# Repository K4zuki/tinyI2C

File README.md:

tinyI2C{-}
=======

This is a tiny UART-I2C converter software/hardware project using mbed conpatible microcontrollers.
The module converts UART command packets into I2C/SPI protocol or GPIO to read/write with
configurable pull-up/pull-down modes.

- the "FTDI" USB-UART cable to connect to host PC; from PC the module look only an USB-Serial port
    - up to 115200 boudrate UART to communicate
- up to 4 channel I2C ports with selectable speed
- one SPI port with 8/16 bits word, also selectable speed
- up to 2 x 8bit, General Purpose IO ports

```
TinyI2C/         <-- root
├── doc/      <-- document source
├── gui/      <-- PyQt4 based GUI source codes
├── mbed/     <-- mbed source codes
├── pcb/      <-- PCB design files for eagle
└── python/   <-- python module code with standalone test program
```

# Requirement
- Python 3
  `apt-get install python3`
- PySerial
  `pip3 install pyserial`
* mbed microcontrollers using LPC824(recommended)/LPC1768/LPC11U24/LPC11U35
  see [mbed.org](developer.mbed.org)

# Install
1. install python 3.3+ on your PC
2. install PySerial
3. (Windows only) if you use LpcXpresso 824 then install [mbed Serial port driver](http://developer.mbed.org/handbook/Windows-serial-configuration)

# Usage
1. write mbed program into your mbed
2. connect mbed to PC via Serial port
3. start gui software
4. select Serial port from dropdown list
5. you will be able to use up to 4 channels of I2C slaves and more!
    * check PinOut for your usage! 

# Demo
  try `python/test.py`

## Demo GUI
GUI source codes placed in `gui/` which requires compilation
 (for now, _do it yourself_ basis).

GUI setup requires:

- PyQt5
- pyinstaller

```
$ pip3 install pyqt5 pyinstaller
```

### Compile GUI
On project root,
```
$ make gui
```

### Run GUI
On project root,
```
$ dist/TinyI2C
```

# Command set and protocol
- _this command character as well as packet structure is inspired(some copied) from
NXP Semiconductor's UART-I2C converter/controller, named **SC18IM700**._

- the command packet starts/ends with few number of characters: for starting(`head`)
character there are several choices but ending(`tail`) is always `'P'`, 0x50 in hex.
    - if only sending 'P', `tinyI2C` makes stop condition pulse (**without start condition**)
  on currently selected I2C bus and returns "ok" return packet.
- the `tinyI2C` watches its UART port \_Forever until_ it receives `tail`
  and counts received packet length by bytes (`plength`).
  then searches first character of the packet whether if matches one of registered `head` character.
    - if it does not match with any of valid `head` the device returns
  "command is not implemented" return packet.
- if valid head found it checks `plength-2` which is actual data packet length.
    - if you send an invalid packet, the device returns "bad packet" return packet.

## I2C
### `'S'` 0x53 I2C-bus START
### `'P'` 0x50 I2C-bus STOP, end of packet
- the protocol starts from `'S'`, which makes start condition on I2C bus, followed by 7bit I2C slave address and read(1)/write(0) command bit and,
  - to *Write* data into slave device: send data length to write(1~255) and actual data
  - to *Read* data from slave device: send data length to read(1~255)
- ends with sending `'P'` which makes stop condition on the bus
- return packet depends on command:
  - first, `"ACK"` or `"NAK"` depends on response from slave
  - *Read*: read data in hex sting (0xAA -> "AA") separated by ',' and ends by `ok`
  - *Write*: `ok`

- command packet: write 4 bytes to slave at 0x80(8bit)

| head  | slave address(W) | data length |          binary data to write           | tail  |
|:-----:|:----------------:|:-----------:|:---------------------------------------:|:-----:|
|   S   |    0x\_8 \_0     |  0x\_0 \_4  |    0x_D \_E \_A \_D \_B \_E \_A \_F     |   P   |
| `'S'` |      `'80'`      |   `'04'`    |              `'=>:=;>:?'`               | `'P'` |
| 0x53  |    0x38 0x30     |  0x30 0x34  | 0x3D 0x3E 0x3A 0x3D 0x3B 0x3E 0x3A 0x3F | 0x50  |

- return packet

| result | head  | delimiter | tail |
|:------:|:-----:|:---------:|:----:|
| sucess | "ACK" |     ,     | "ok" |
|  fail  | "NAK" |     ,     | "ok" |

- command packet: read 4 bytes from slave at 0x80(8bit)

| head | slave address(R\) | data length | tail |
|:----:|:-----------------:|:-----------:|:----:|
|  S   |     0x\_8 \_1     |  0x\_0 \_4  |  P   |

- return packet

| result | head  | delimiter |               data                | tail |
|:------:|:-----:|:---------:|:---------------------------------:|:----:|
| sucess | "ACK" |     ,     | actual data: "AA","BB","CC","DD", | "ok" |
|  fail  | "NAK" |     ,     | dummy data: "C4","FE","E0","CA",  | "ok" |

- command packet: write and read 4 bytes to/from slave at 0x80(8bit)

| head | slave address(W) | data length |       binary data to write       | repeated start | slave address(R\) | data length | tail |
|:----:|:----------------:|:-----------:|:--------------------------------:|:--------------:|:-----------------:|:-----------:|:----:|
|  S   |    0x\_8 \_0     |  0x\_0 \_4  | 0x_D \_E \_A \_D \_B \_E \_A \_F |       S        |     0x\_8 \_1     |  0x\_0 \_4  |  P   |

- return packet

| result | head  | delimiter |               data                | tail |
|:------:|:-----:|:---------:|:---------------------------------:|:----:|
| sucess | "ACK" |     ,     | actual data: "AA","BB","CC","DD", | "ok" |
|  fail  | "NAK" |     ,     | dummy data: "C4","FE","E0","CA",  | "ok" |

### `'C'` 0x43 change channel
- you can select I2C channel by sending `'C'` and channel number `'0'`to`'3'` with `tail` char.

| head | channel | tail |
|:----:|:-------:|:----:|
|  C   |   '0'   |  P   |
|  C   |   '1'   |  P   |
|  C   |   '2'   |  P   |
|  C   |   '3'   |  P   |

## SPI
### `'E'` 0x45 SPI transfer start

- minimum plength=8

| head | data length(W) | data length(R\) | binary data to write | tail |
|:----:|:--------------:|:---------------:|:--------------------:|:----:|
|  E   |   0x\_0 \_1    |    0x\_0 \_0    |      0x\_D \_E       |  P   |

- minimum plength=10(16bit)

| head | data length(W) | data length(R\) | binary data to write | tail |
|:----:|:--------------:|:---------------:|:--------------------:|:----:|
|  E   |   0x\_0 \_1    |    0x\_0 \_0    |   0x_D \_E \_A \_D   |  P   |

- write and read

| head | data length(W) | data length(R\) |       binary data to write       | tail |
|:----:|:--------------:|:---------------:|:--------------------------------:|:----:|
|  E   |   0x\_0 \_4    |    0x\_0 \_4    | 0x_D \_E \_A \_D \_B \_E \_A \_F |  P   |

<!--
~~~
/*
"0|   1   2|   3   4|   5   6  7  8  9 10 11 12|13" //plength=14
"E| 0x\_0 \_1| 0x\_0 \_0| 0x_D \_E| P"                   //minimum plength=8
"E| 0x\_0 \_1| 0x\_0 \_0| 0x_D \_E|_A \_D| P"             //minimum plength=10(16bit)
"E| 0x\_0 \_4| 0x\_0 \_0| 0x_D \_E \_A \_D \_B \_E \_A \_F| P" //write
"E| 0x\_0 \_4| 0x\_0 \_4| 0x_D \_E \_A \_D \_B \_E \_A \_F| P" //write and read
*/
~~~
-->

## GPIO
This is a subset of [R/W commands](#internal-registers); only access GPIO's status registers.

### `'I'` 0x49 read GPIO port register
### `'O'` 0x4F write to GPIO port register

| head | GPIO | tail |
|:----:|:----:|:----:|
|  I   | '0'  |  P   |
|  I   | '1'  |  P   |

| head | GPIO |   data    | tail |
|:----:|:----:|:---------:|:----:|
|  O   | '0'  | 0x\_A \_A |  P   |
|  O   | '1'  | 0x\_A \_A |  P   |

| register | name in python | purpose          |
|:--------:|:--------------:|:-----------------|
|    0     |   GPIO0_STAT   | status of GPIO 0 |
|    1     |   GPIO1_STAT   | status of GPIO 1 |

## Internal registers
### `'R'` 0x52 read internal register
### `'W'` 0x57 write to internal register
- single register read

| head | register | tail |
|:----:|:--------:|:----:|
|  R   |   '0'    |  P   |
|  R   |   '1'    |  P   |

- multi registers read

| head | register(1) | register(2) | ... | register(n) | tail |
|:----:|:-----------:|:-----------:|:---:|:-----------:|:----:|
|  R   |     '0'     |     '1'     | ... |     '5'     |  P   |
|  R   |     '1'     |     '0'     | ... |     '9'     |  P   |

- return packet's order is same as command packet's order

: multi registers write

| head | register(1) | register data (1) | register(2) | register data (2) | ... | register(n) | register data (n) | tail |
|:----:|:-----------:|:-----------------:|:-----------:|:-----------------:|:---:|:-----------:|:-----------------:|:----:|
|  W   |     '0'     |     0x\_A \_A     |     '1'     |     0x\_A \_B     | ... |     '5'     |     0x\_A \_D     |  P   |
|  W   |     '1'     |     0x\_A \_A     |     '0'     |     0x\_A \_B     | ... |     '9'     |     0x\_A \_D     |  P   |

- return packet's order is same as command packet's order

| register | name in python | purpose                              |
|:--------:|:--------------:|:-------------------------------------|
|    0     |    CHIP_ID     | converter's chip ID                  |
|    1     |   GPIO0_STAT   | status of GPIO 0                     |
|    2     |   GPIO1_STAT   | status of GPIO 1                     |
|    4     |   GPIO1_CONF   | GPIO 0 IO configuration              |
|    3     |   GPIO0_CONF   | GPIO 1 IO configuration              |
|    5     |    I2C_CONF    | I2C channel 1~4 speed configuration  |
|    6     |    SPI_CONF    | SPI speed and polarity configuration |

| register 0  | command | CHIP_ID                    |
|:-----------:|:-------:|:---------------------------|
| [7\.\.\.0\] |   R/W   | returns chip ID character: |
|             |         | '0'- LPC824                |
|             |         | '1'- LPC1768               |
|             |         | '2'- LPC11U24 or LPC11U35  |

| register 1  | command | GPIO0_STAT                                                          |
|:-----------:|:-------:|:--------------------------------------------------------------------|
| [7\.\.\.0\] |    R    | behavior changes depend on corresponding bit of GPIO0_CONF register |
|             |         | 1: reads output setting                                             |
|             |         | 0: reads input of the pin                                           |
|             |    W    | behavior changes depend on corresponding bit of GPIO0_CONF register |
|             |         | 1: writes data to the pin                                           |
|             |         | 0: do nothing                                                       |

| register 2  | command | GPIO1_STAT                                                           |
|:-----------:|:-------:|:---------------------------------------------------------------------|
|             |         | **if GPIO1 is not enabled, access to this register will be ignored** |
| [7\.\.\.0\] |    R    | behavior changes depend on corresponding bit of GPIO1_CONF register  |
|             |         | 1: reads output setting                                              |
|             |         | 0: reads input of the pin                                            |
|             |    W    | behavior changes depend on corresponding bit of GPIO1_CONF register  |
|             |         | 1: writes data to the pin                                            |
|             |         | 0: do nothing                                                        |

| register 3  | command | GPIO0_CONF                                                                                    |
|:-----------:|:-------:|:----------------------------------------------------------------------------------------------|
| [7\.\.\.0\] |    R    | Reads each pin's Input/Output conditions:                                                     |
|             |         | 1 = the pin is set to output                                                                  |
|             |         | 0 = the pin is set to input with internal pullup                                              |
|             |    W    | Sets each pin's Input/Output configurations:                                                  |
|             |         | 1: sets the pin to an Output. output level is set by corresponding bit of GPIO0_STAT register |
|             |         | 0: sets the pin to an Input with internal pull-up connected                                   |

| register 4  | command | GPIO1_CONF                                                                                    |
|:-----------:|:-------:|:----------------------------------------------------------------------------------------------|
|             |         | **if GPIO1 is not enabled, access to this register will be ignored**                          |
| [7\.\.\.0\] |    R    | Reads each pin's Input/Output conditions:                                                     |
|             |         | 1: the pin is set to output                                                                   |
|             |         | 0: the pin is set to input with internal pullup                                               |
|             |    W    | Sets each pin's Input/Output configurations:                                                  |
|             |         | 1: sets the pin to an Output. output level is set by corresponding bit of GPIO1_STAT register |
|             |         | 0: sets the pin to an Input with internal pull-up connected                                   |

| register 5  | command | I2C_CONF                                                                                                    |
|:-----------:|:-------:|:------------------------------------------------------------------------------------------------------------|
| [7\.\.\.6\] |   R/W   | Read/Write clock configuration of I2C1                                                                      |
|             |         | 11: I2C1 is set to operate in 800kHz clock                                                                  |
|             |         | 10: I2C1 is set to operate in 600kHz clock                                                                  |
|             |         | 01: I2C1 is set to operate in 400kHz clock                                                                  |
|             |         | 00: I2C1 is set to operate in 200kHz clock                                                                  |
| [5\.\.\.4\] |         | Read/Write clock configuration of I2C2; **if I2C2 is not enabled, access to this bitfield will be ignored** |
|             |         | 11: I2C2 is set to operate in 400kHz clock                                                                  |
|             |         | 10: I2C2 is set to operate in 300kHz clock                                                                  |
|             |         | 01: I2C2 is set to operate in 200kHz clock                                                                  |
|             |         | 00: I2C2 is set to operate in 100kHz clock                                                                  |
| [3\.\.\.2\] |         | Read/Write clock configuration of I2C3; **if I2C3 is not enabled, access to this bitfield will be ignored** |
|             |         | 11: I2C3 is set to operate in 400kHz clock                                                                  |
|             |         | 10: I2C3 is set to operate in 300kHz clock                                                                  |
|             |         | 01: I2C3 is set to operate in 200kHz clock                                                                  |
|             |         | 00: I2C3 is set to operate in 100kHz clock                                                                  |
| [1\.\.\.0\] |         | Read/Write clock configuration of I2C4; **if I2C4 is not enabled, access to this bitfield will be ignored** |
|             |         | 11: I2C4 is set to operate in 400kHz clock                                                                  |
|             |         | 10: I2C4 is set to operate in 300kHz clock                                                                  |
|             |         | 01: I2C4 is set to operate in 200kHz clock                                                                  |
|             |         | 00: I2C4 is set to operate in 100kHz clock                                                                  |

| register 6  | command | SPI_CONF                                  |
|:-----------:|:-------:|:------------------------------------------|
|    [7\]     |   R/W   | Not used                                  |
| [6\.\.\.4\] |         | Read/Write clock configuration of SPI     |
|             |         | 111: SPI is set to operate in 8MHz clock  |
|             |         | 110: SPI is set to operate in 7MHz clock  |
|             |         | ...                                       |
|             |         | 001: SPI is set to operate in 2MHz clock  |
|             |         | 000: SPI is set to operate in 1MHz clock  |
|    [3\]     |         | Reads/Wreite polarity of CE print         |
|             |         | 1: CE is set to HIGH-active               |
|             |         | 0: CE is set to LOW-active                |
|    [2\]     |         | Read/Write word size setting of SPI       |
|             |         | 1: 16 bit word                            |
|             |         | 0: 8 bit word                             |
| [1\.\.\.0\] |         | Read/Write SPI mode                       |
|             |         | 11: SPI is set to operate in clock mode 3 |
|             |         | 10: SPI is set to operate in clock mode 2 |
|             |         | 01: SPI is set to operate in clock mode 1 |
|             |         | 00: SPI is set to operate in clock mode 0 |

# Contribution by
Kazuki Yamamoto ( <k.yamamoto.08136891@gmail.com> )

# License
- [CC-BY-SA](http://creativecommons.org/licenses/by-sa/4.0/legalcode)
- [CC-BY-SA 日本語](http://creativecommons.org/licenses/by-sa/2.1/jp/legalcode)

# Author

[K4zuki](https://github.com/K4zuki)

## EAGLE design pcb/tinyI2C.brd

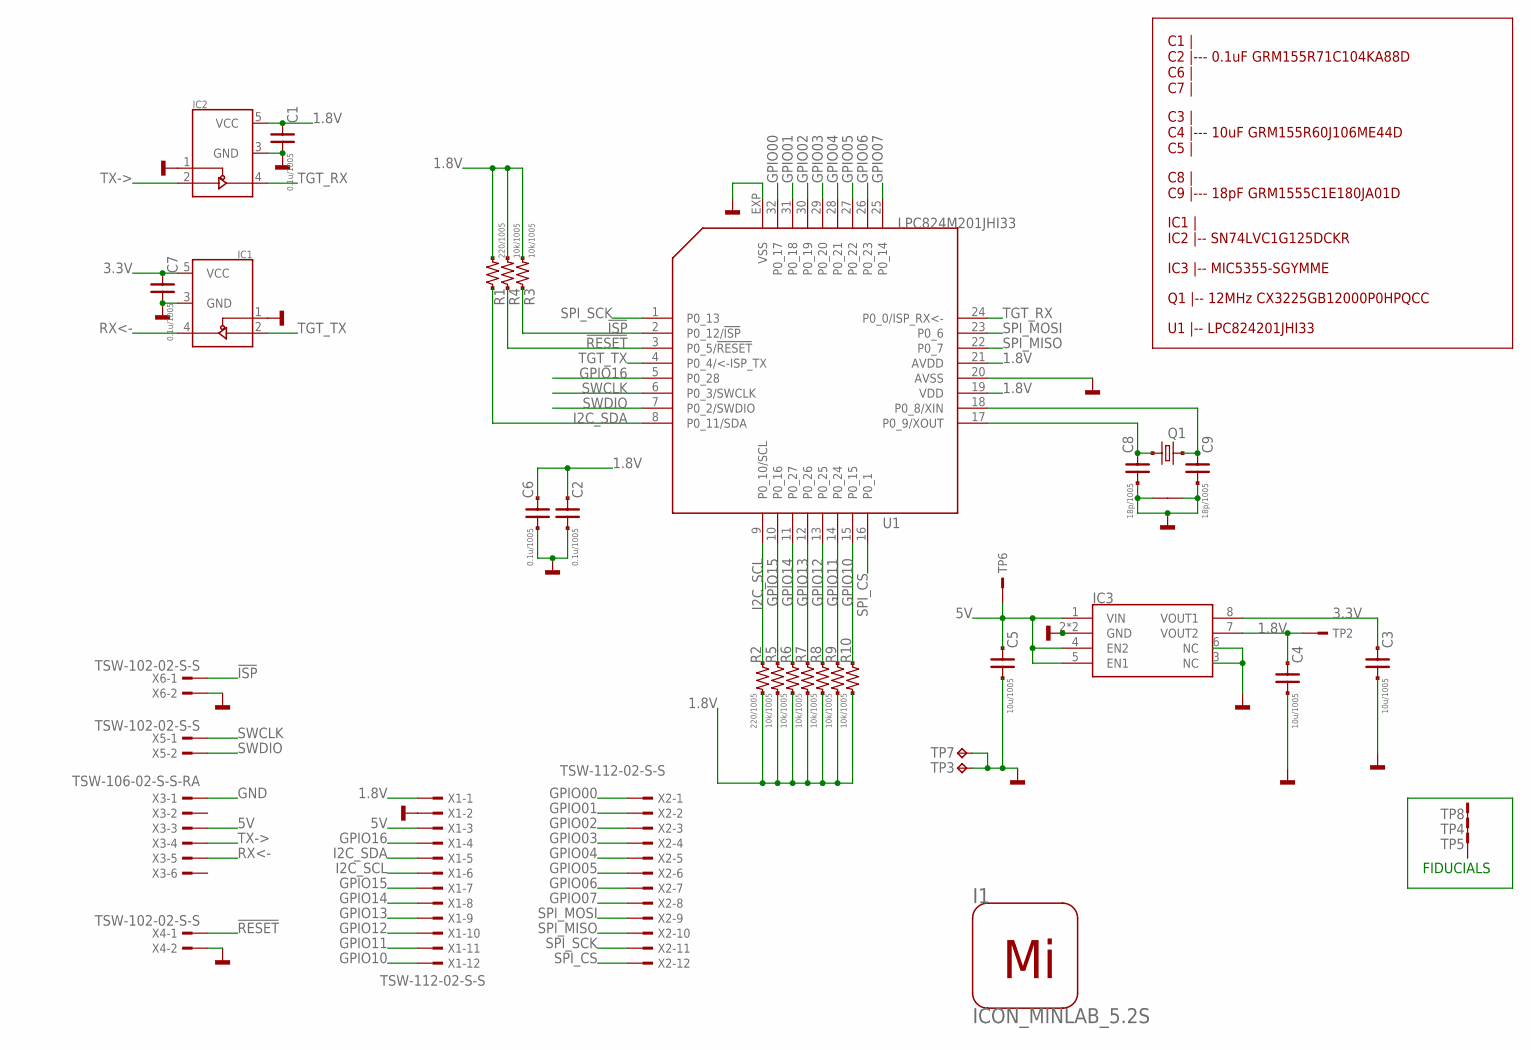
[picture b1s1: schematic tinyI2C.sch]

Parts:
C1, C2, C6, C7: 0.1u/1005; C0402
C3, C4, C5: 10u/1005; C0402
C8, C9: 18p/1005; C0402
I1: ICON_MINLAB_5.2S; ICON_MINLAB_5.2MM
IC1, IC2: 74LVC1G125_SC70; IC_05_0.635_40MIL
IC3: IC_LDO_MIC5355_3.3/1.8; IC_08_0.65_160MIL_EP
Q1: CRYSTAL4_12M_3225; CLOCK_3225
R1, R2: 220/1005; C0402
R3, R4, R5, R6, R7, R8, R9, R10: 10k/1005; C0402
TP2, TP6: TESTPAD; TP06RECT
TP3, TP7: TPTP14R; TP14R
TP4, TP5, TP8: TESTPAD_F; FIDUCIAL
U1: LPC824M201JHI33; HVQFN33
X1, X2: TSW-112-02-S-S
X3: TSW-106-02-S-S-RA
X4, X5, X6: TSW-102-02-S-S

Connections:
1.8V: C1.1, C2.1, C4.1, C6.1, IC2.5 (VCC), IC3.7 (VOUT2), R1.2, R2.2, R3.2, R4.2, R5.2, R6.2, R7.2, R8.2, R9.2, R10.2, TP2.TP, U1.19 (VDD), U1.21 (AVDD), X1.1
3.3V: C3.1, C7.1, IC1.5 (VCC), IC3.8 (VOUT1)
5V: C5.1, IC3.1 (VIN), IC3.4 (EN2), IC3.5 (EN1), TP6.TP, X1.3, X3.3
!ISP!: R3.1, U1.2 (P0_12/!ISP!), X6.1
!RESET!: R4.1, U1.3 (P0_5/!RESET!), X4.1
GND: C1.2, C2.2, C3.2, C4.2, C5.2, C6.2, C7.2, C8.2, C9.2, IC1.1 (!OE!), IC1.3 (GND), IC2.1 (!OE!), IC2.3 (GND), IC3.2 (GND), IC3.3 (NC), IC3.6 (NC), IC3.EXP (GND), Q1.2, Q1.4, TP3.TP, TP7.TP, U1.20 (AVSS), U1.EXP (VSS), X1.2, X3.1, X4.2, X6.2
GPIO00: U1.32 (P0_17), X2.1
GPIO01: U1.31 (P0_18), X2.2
GPIO02: U1.30 (P0_19), X2.3
GPIO03: U1.29 (P0_20), X2.4
GPIO04: U1.28 (P0_21), X2.5
GPIO05: U1.27 (P0_22), X2.6
GPIO06: U1.26 (P0_23), X2.7
GPIO07: U1.25 (P0_14), X2.8
GPIO10: R10.1, U1.15 (P0_15), X1.12
GPIO11: R9.1, U1.14 (P0_24), X1.11
GPIO12: R8.1, U1.13 (P0_25), X1.10
GPIO13: R7.1, U1.12 (P0_26), X1.9
GPIO14: R6.1, U1.11 (P0_27), X1.8
GPIO15: R5.1, U1.10 (P0_16), X1.7
GPIO16: U1.5 (P0_28), X1.4
I2C_SCL: R2.1, U1.9 (P0_10/SCL), X1.6
I2C_SDA: R1.1, U1.8 (P0_11/SDA), X1.5
unnamed: C8.1, Q1.1, U1.17 (P0_9/XOUT)
unnamed: C9.1, Q1.3 (2), U1.18 (P0_8/XIN)
RX<-: IC1.4 (Y), X3.5
SPI_CS: U1.16 (P0_1), X2.12
SPI_MISO: U1.22 (P0_7), X2.10
SPI_MOSI: U1.23 (P0_6), X2.9
SPI_SCK: U1.1 (P0_13), X2.11
SWCLK: U1.6 (P0_3/SWCLK), X5.1
SWDIO: U1.7 (P0_2/SWDIO), X5.2
TGT_RX: IC2.4 (Y), U1.24 (P0_0/ISP_RX<-)
TGT_TX: IC1.2 (A), U1.4 (P0_4/<-ISP_TX)
TX->: IC2.2 (A), X3.4

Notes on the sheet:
FIDUCIALS
C1 | C2 |--- 0.1uF GRM155R71C104KA88D C6 | C7 |
C3 | C4 |--- 10uF GRM155R60J106ME44D C5 |
IC1 | IC2 |-- SN74LVC1G125DCKR
IC3 |-- MIC5355-SGYMME
U1 |-- LPC824201JHI33
C8 | C9 |--- 18pF GRM1555C1E180JA01D
Q1 |-- 12MHz CX3225GB12000P0HPQCC

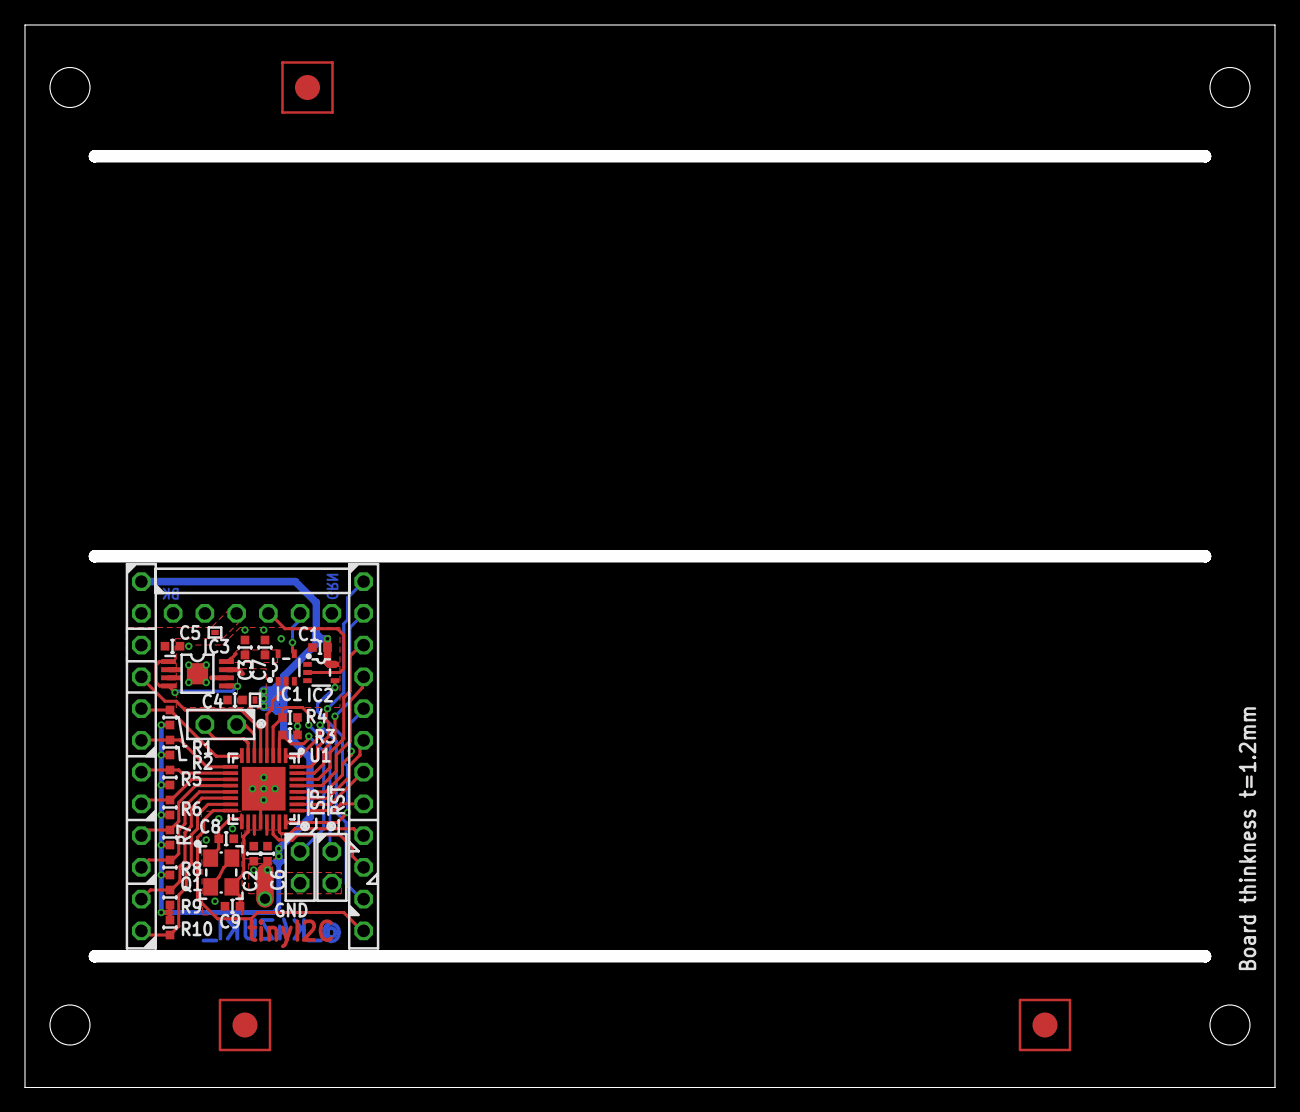
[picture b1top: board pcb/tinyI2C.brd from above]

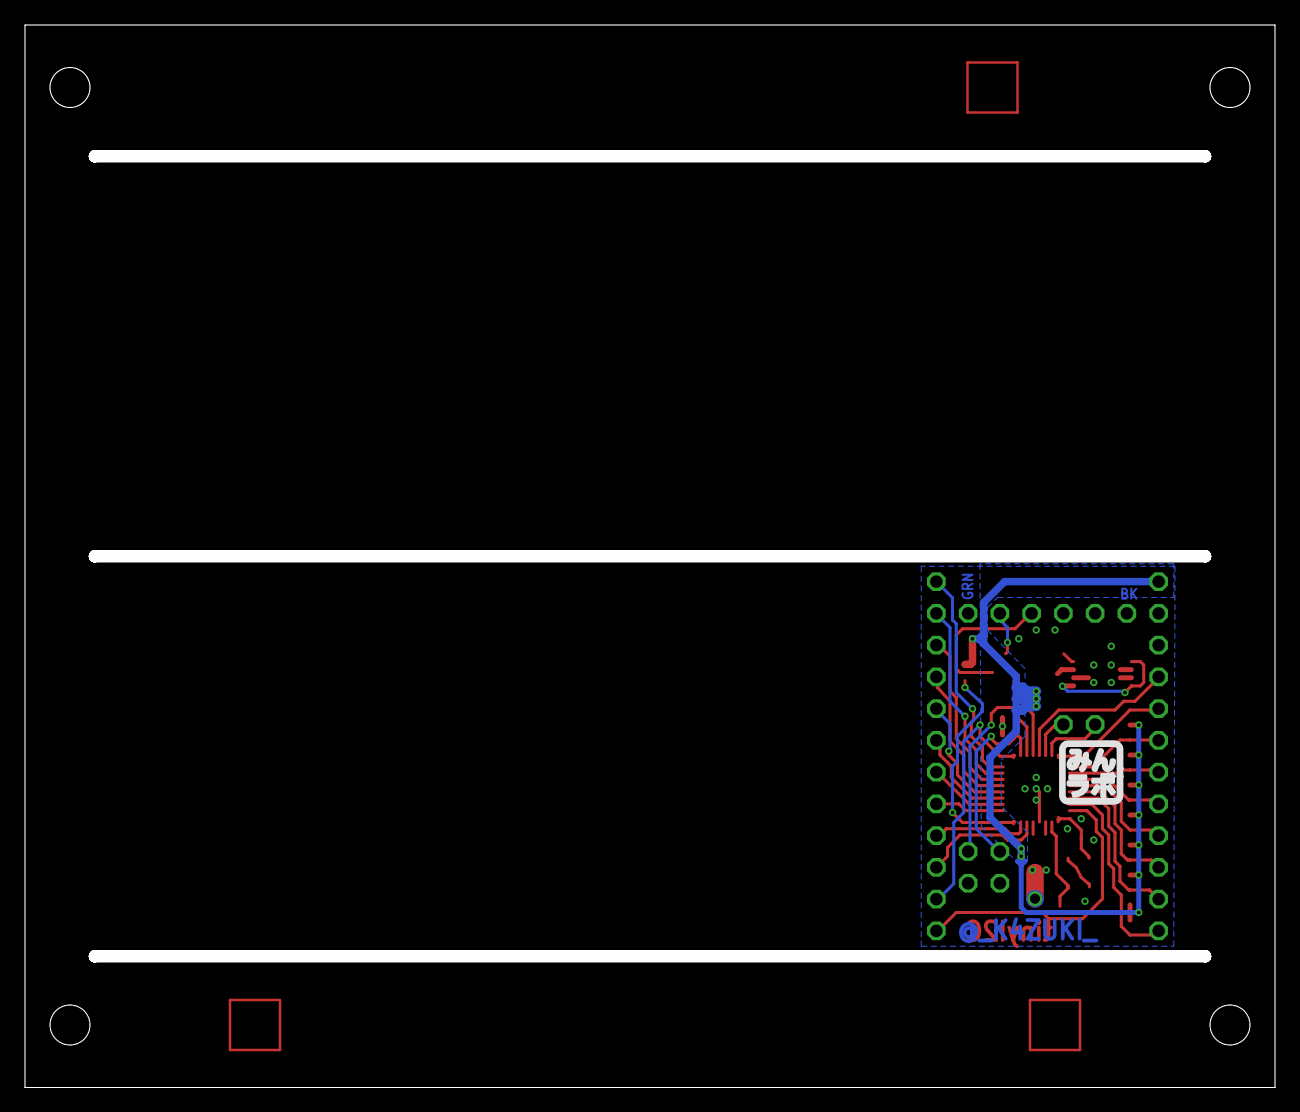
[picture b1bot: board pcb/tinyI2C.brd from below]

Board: 2 copper layers, 100.0 x 85.0 mm, 38 parts (2 on the bottom side), 35 nets.

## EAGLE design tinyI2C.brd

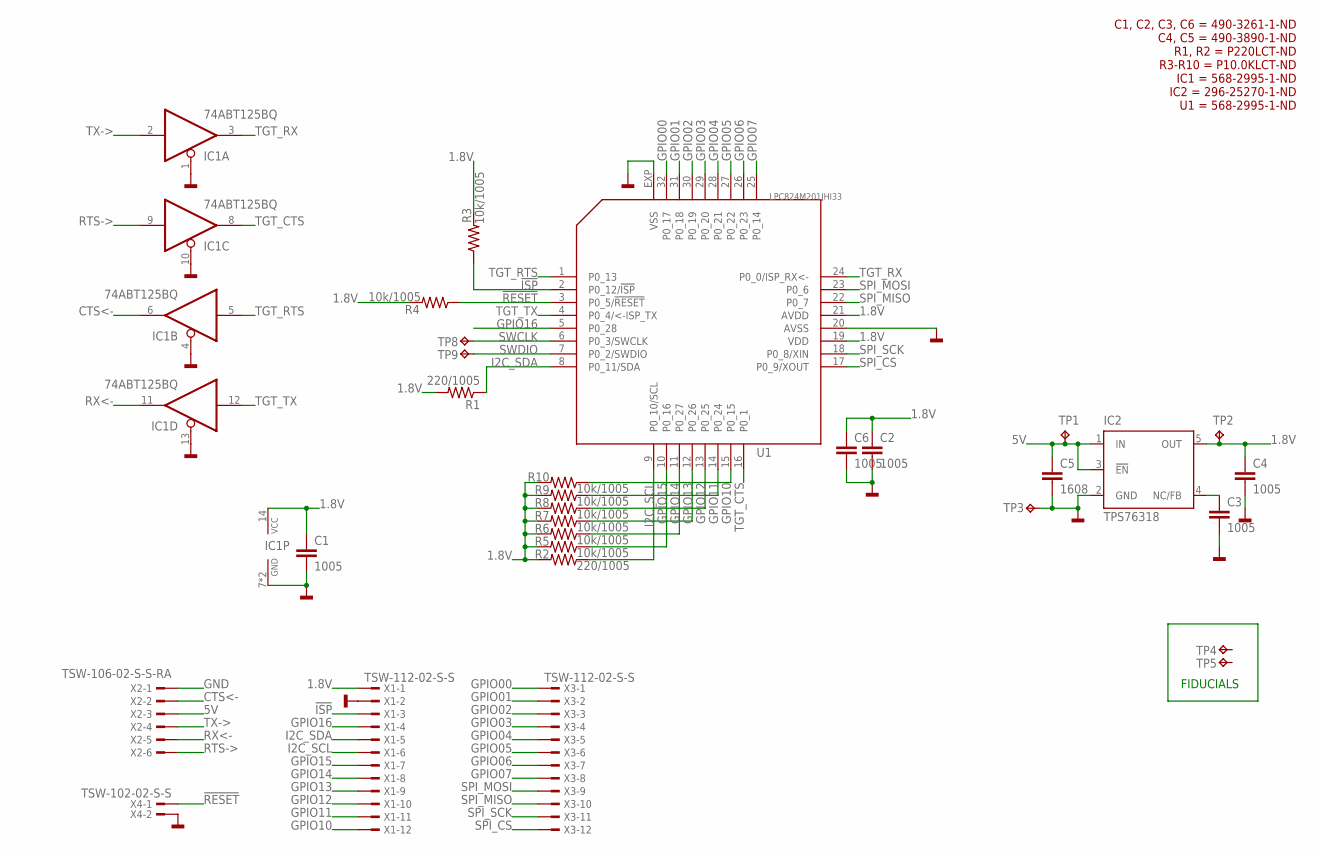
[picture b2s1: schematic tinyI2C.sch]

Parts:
C1, C2, C3, C4, C6: 1005; C1005
C5: 1608; C1608
IC1: 74ABT125BQ; DHVQFN14
IC2: TPS76318; SOT23-DBV
R1, R2: 220/1005; R1005
R3, R4, R5, R6, R7, R8, R9, R10: 10k/1005; R1005
TP1, TP2, TP3, TP8, TP9: TPTP07R; TP07R
TP4, TP5: TPTP10R; TP10R
U1: LPC824M201JHI33; HVQFN33
X1, X3: TSW-112-02-S-S
X2: TSW-106-02-S-S-RA
X4: TSW-102-02-S-S

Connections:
1.8V: C1.1, C2.1, C4.1, C6.1, IC1.14 (VCC), IC2.5 (OUT), R1.2, R2.2, R3.2, R4.2, R5.2, R6.2, R7.2, R8.2, R9.2, R10.2, TP2.TP, U1.19 (VDD), U1.21 (AVDD), X1.1
5V: C5.1, IC2.1 (IN), IC2.3 (!EN), TP1.TP, X2.3
!ISP!: R3.1, U1.2 (P0_12/!ISP!), X1.3
!RESET!: R4.1, U1.3 (P0_5/!RESET!), X4.1
CTS<-: IC1.6 (O), X2.2
GND: C1.2, C2.2, C3.2, C4.2, C5.2, C6.2, IC1.1 (OE), IC1.4 (OE), IC1.7 (GND), IC1.10 (OE), IC1.13 (OE), IC1.EXP (GND), IC2.2 (GND), TP3.TP, U1.20 (AVSS), U1.EXP (VSS), X1.2, X2.1, X4.2
GPIO00: U1.32 (P0_17), X3.1
GPIO01: U1.31 (P0_18), X3.2
GPIO02: U1.30 (P0_19), X3.3
GPIO03: U1.29 (P0_20), X3.4
GPIO04: U1.28 (P0_21), X3.5
GPIO05: U1.27 (P0_22), X3.6
GPIO06: U1.26 (P0_23), X3.7
GPIO07: U1.25 (P0_14), X3.8
GPIO10: R10.1, U1.15 (P0_15), X1.12
GPIO11: R9.1, U1.14 (P0_24), X1.11
GPIO12: R8.1, U1.13 (P0_25), X1.10
GPIO13: R7.1, U1.12 (P0_26), X1.9
GPIO14: R6.1, U1.11 (P0_27), X1.8
GPIO15: R5.1, U1.10 (P0_16), X1.7
GPIO16: U1.5 (P0_28), X1.4
I2C_SCL: R2.1, U1.9 (P0_10/SCL), X1.6
I2C_SDA: R1.1, U1.8 (P0_11/SDA), X1.5
unnamed: C3.1, IC2.4 (NC/FB)
RTS->: IC1.9 (I), X2.6
RX<-: IC1.11 (O), X2.5
SPI_CS: U1.17 (P0_9/XOUT), X3.12
SPI_MISO: U1.22 (P0_7), X3.10
SPI_MOSI: U1.23 (P0_6), X3.9
SPI_SCK: U1.18 (P0_8/XIN), X3.11
SWCLK: TP8.TP, U1.6 (P0_3/SWCLK)
SWDIO: TP9.TP, U1.7 (P0_2/SWDIO)
TGT_CTS: IC1.8 (O), U1.16 (P0_1)
TGT_RTS: IC1.5 (I), U1.1 (P0_13)
TGT_RX: IC1.3 (O), U1.24 (P0_0/ISP_RX<-)
TGT_TX: IC1.12 (I), U1.4 (P0_4/<-ISP_TX)
TX->: IC1.2 (I), X2.4

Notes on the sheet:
FIDUCIALS
C1, C2, C3, C6 = 490-3261-1-ND C4, C5 = 490-3890-1-ND R1, R2 = P220LCT-ND R3-R10 = P10.0KLCT-ND IC1 = 568-2995-1-ND IC2 = 296-25270-1-ND U1 = 568-2995-1-ND

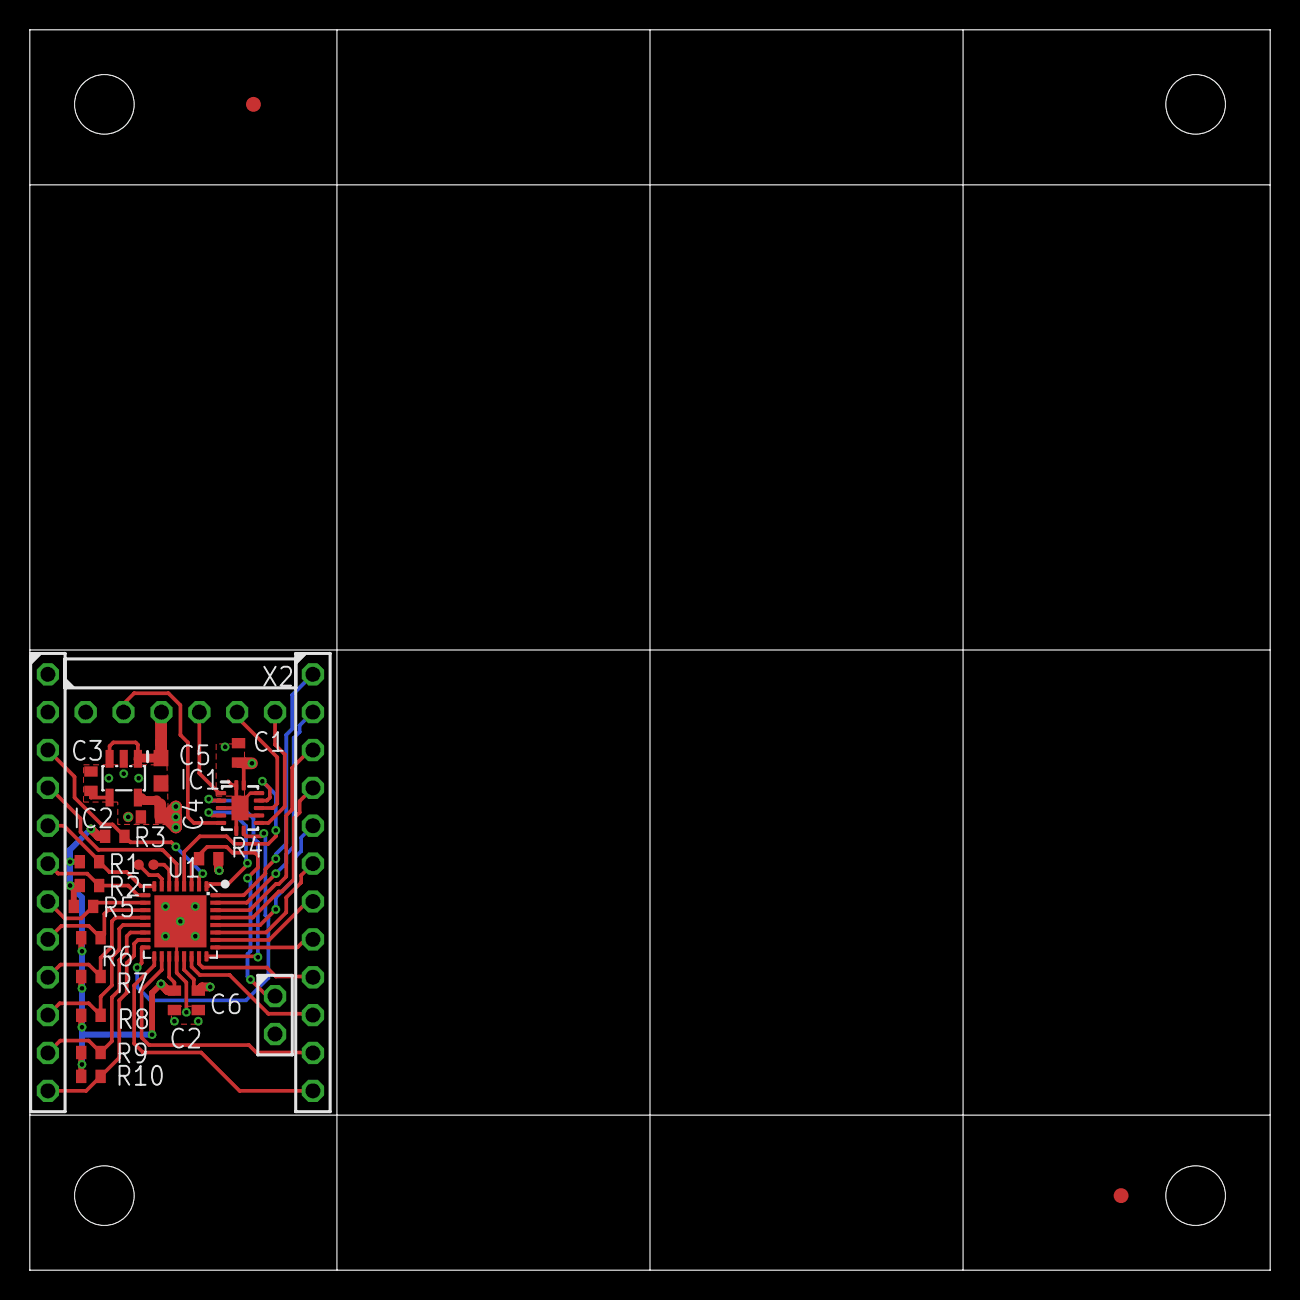
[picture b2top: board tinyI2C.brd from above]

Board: 2 copper layers, 83.2 x 83.2 mm, 30 parts (0 on the bottom side), 37 nets.

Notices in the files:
README.md:
License:
- [CC-BY-SA](http://creativecommons.org/licenses/by-sa/4.0/legalcode)
- [CC-BY-SA 日本語](http://creativecommons.org/licenses/by-sa/2.1/jp/legalcode)
